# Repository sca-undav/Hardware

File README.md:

# Hardware para sistemas de control
Desarrollos didácticos de circuitos para las prácticas de control.

Se incluye:
- Accionador CC-20A. Diseñado con un mosfet IRFZ48N y optoacoplador, para su uso mediante modulación de ancho de pulso. Entrada de 5 VDC y salida de 20 A máximos en corriente continua. 
- Accionador AC-10A. Relé de estado sólido diseñado con un triac BTA12-600C y optoacoplador. Entrada de 5 VDC y salida alterna de 10 A.

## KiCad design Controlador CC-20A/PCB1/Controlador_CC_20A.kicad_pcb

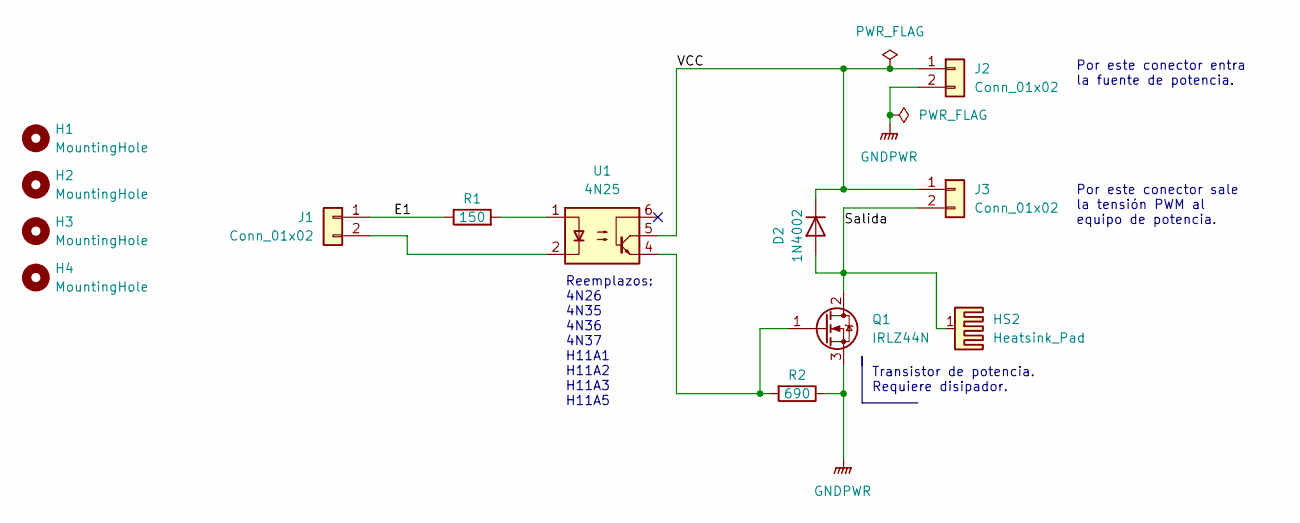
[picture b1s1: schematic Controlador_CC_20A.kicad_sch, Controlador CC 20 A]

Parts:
D2: 1N4002; D_A-405_P5.08mm_Vertical_KathodeUp
H1, H2, H3, H4: MountingHole; MountingHole_3.5mm
HS2: Heatsink_Pad; Heatsink_Fischer_SK104-STC-STIC_35x13mm_2xDrill2.5mm
J1: Conn_01x02; PinHeader_1x02_P2.54mm_Vertical
J2, J3: Conn_01x02; TerminalBlock_MetzConnect_Type094_RT03502HBLU_1x02_P5.00mm_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
Q1: IRLZ44N; TO-220-3_Vertical
R1: 150; R_Axial_DIN0207_L6.3mm_D2.5mm_P7.62mm_Horizontal
R2: 690; R_Axial_DIN0309_L9.0mm_D3.2mm_P12.70mm_Horizontal
U1: 4N25; DIP-6_W7.62mm

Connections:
/E1: J1.1, R1.1
/Salida: D2.2 (A), HS2.1, J3.2, Q1.2 (D)
/VCC: D2.1 (K), J2.1, J3.1, U1.5
GNDPWR: J2.2, Q1.3 (S), R2.1
unnamed: J1.2, U1.2
unnamed: Q1.1 (G), R2.2, U1.4
unnamed: R1.2, U1.1

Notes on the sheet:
Por este conector entra la fuente de potencia.
Transistor de potencia. Requiere disipador.
Reemplazos: 4N26 4N35 4N36 4N37 H11A1 H11A2 H11A3 H11A5
Por este conector sale la tensión PWM al equipo de potencia.

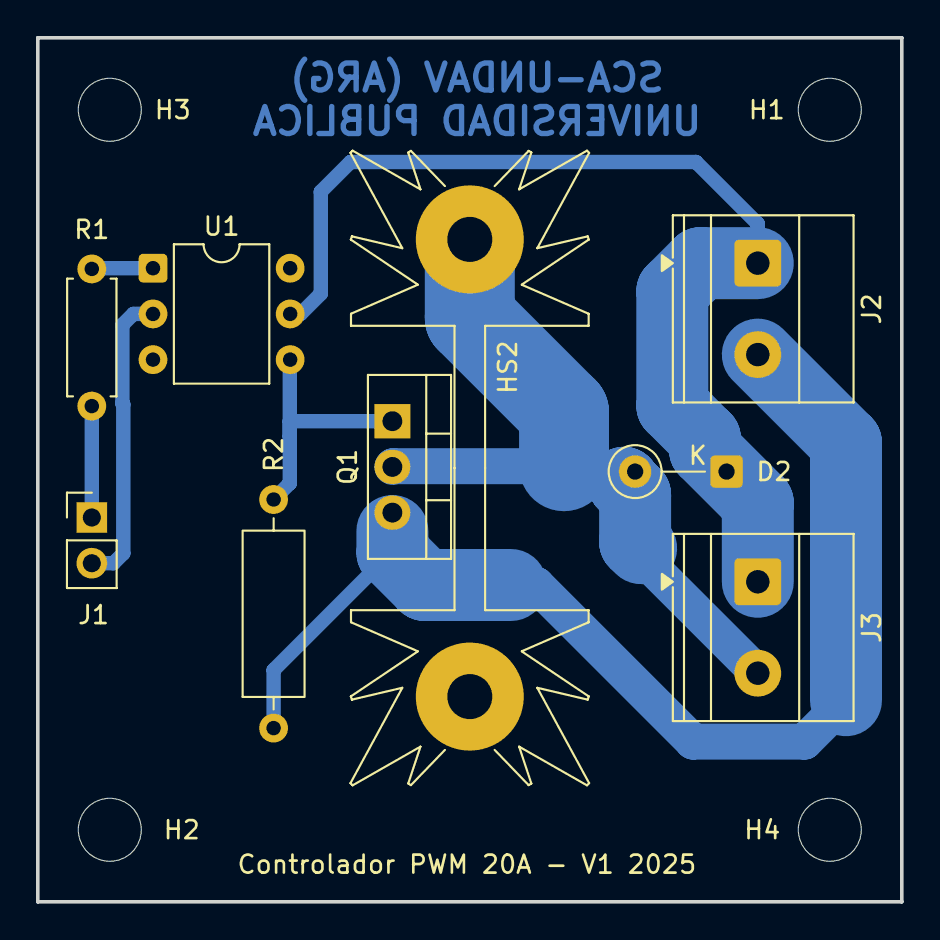
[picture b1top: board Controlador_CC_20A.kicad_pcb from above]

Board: 2 copper layers, 48.0 x 48.0 mm, 13 parts (0 on the bottom side), 7 nets.

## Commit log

2025-05-29 Controladores CC-20A y AC-10A.
2025-07-05 Actualizamos documentos.
2025-07-07 Actualización de hokjas de datos y notas.
2025-07-09 PCB de controlador PWM 20A V1.
2025-07-10 Diseño de PCB V1.
2025-07-10 Actualización de documentación.
2025-11-21 Accionadores eléctricos.
2026-05-08 Correcciones en documentos de accionadores eléctricos.

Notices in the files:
Controlador CC-20A/PCB1/Controlador_CC_20A.kicad_pcb:
Licencia: CERN OHL versión 1.1
Controlador CC-20A/PCB1/Controlador_CC_20A.kicad_sch:
Licencia: CERN OHL versión 25.0
